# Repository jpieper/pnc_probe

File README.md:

# Pocket NC Probe Support #

This repository contains:

* Hardware designs to integrate a https://vers.by touch probe into the Pocket NC, https://pocketnc.com
* g-code routines for performing probe operations on the Pocket NC

# Usage #

When installed, [G38.x gcode commands](https://linuxcnc.org/docs/2.6/html/gcode/gcode.html#sec:G38-probe) work as expected.  If the jpieper/pnc_probe subroutines are installed, two new gcode programs are available: `pnc-probe-center-id` and `pnc-probe-center-od`.

These scripts probe features that are close to machine X=0,Y=0 and set G54 to the exact center.

To run either, manually position the probe along either the X axis or Y axis just inside (for ID) or just outside (for OD) at the depth you wish to probe.  Leave sufficient margin (~2mm) so that when the probe checks other directions it will have room to plunge without colliding with the work.

Then start the program.

# Installation #

## Hardware ##

Watch the following video:

TODO

1. Attach the adapter housing to the A axis stepper using a cable tie.  The cable tie should be pulled tight, as this helps keep the enclosure sealed from chips.

2. Disconnect the RJ45 cable from the A axis carriage and connect it to the bottom RJ45 port on the adapter.  The 1ft long ethernet cable should then be connected from the A axis carriage to the top port of the adapter.

3. To insert the probe, the A axis MUST be moved out of the home position.  Note, the machine CANNOT BE HOMED while the probe is inserted, or it will crash.

4. Using a dial indicator, adjust the M2 screws accessed through holes in the front of the probe to reduce runout at the tip of the probe.

5. Remove the screw cap from the adapter enclosure, attach the probe cable to the USB port.  Note, this is not actual USB, but that is the cable the vers.by ships with.

6. Attach the magnetic coupled end of the cable to the probe.

7. When removing the probe, be sure to reinstall the USB cap, otherwise chips may fall into the connector.

## Software ##

1. Copy the contents of the `ncfiles/` and `subroutines/` directories to `/home/pocketnc` on the pocketnc.  You can use WinSCP from Windows, or rsync from Mac/Linux.  A suitable command for linux might look like:

```
rsync -Pv ncfiles subroutines pocketnc@192.168.6.2:
```

2. Depending upon your machine version, you may need to add a .ini overlay.

### Kinetic ###

Modern versions of the Kinetic interface require no changes.

### Kinetic (pre 5.1.2) ###

Older versions of Kinetic require the following overlay added.

 * Config Tab
 * Server
 * INI OVERLAY
 * EDIT OVERLAY (bottom right)
 * If RS274NGC is not already in the list of groups, use the '+' button to add it.
 * Ensure the following key is set as follows:

```
SUBROUTINE_PATH=/opt/pocketnc/Settings/subroutines:/home/pocketnc/subroutines
```

 * If you had to change anything, click "REBOOT MACHINE".

### Legacy ###

TODO

# LICENSE #

All files contained in this repository are available under an Apache 2.0 License: https://www.apache.org/licenses/LICENSE-2.0

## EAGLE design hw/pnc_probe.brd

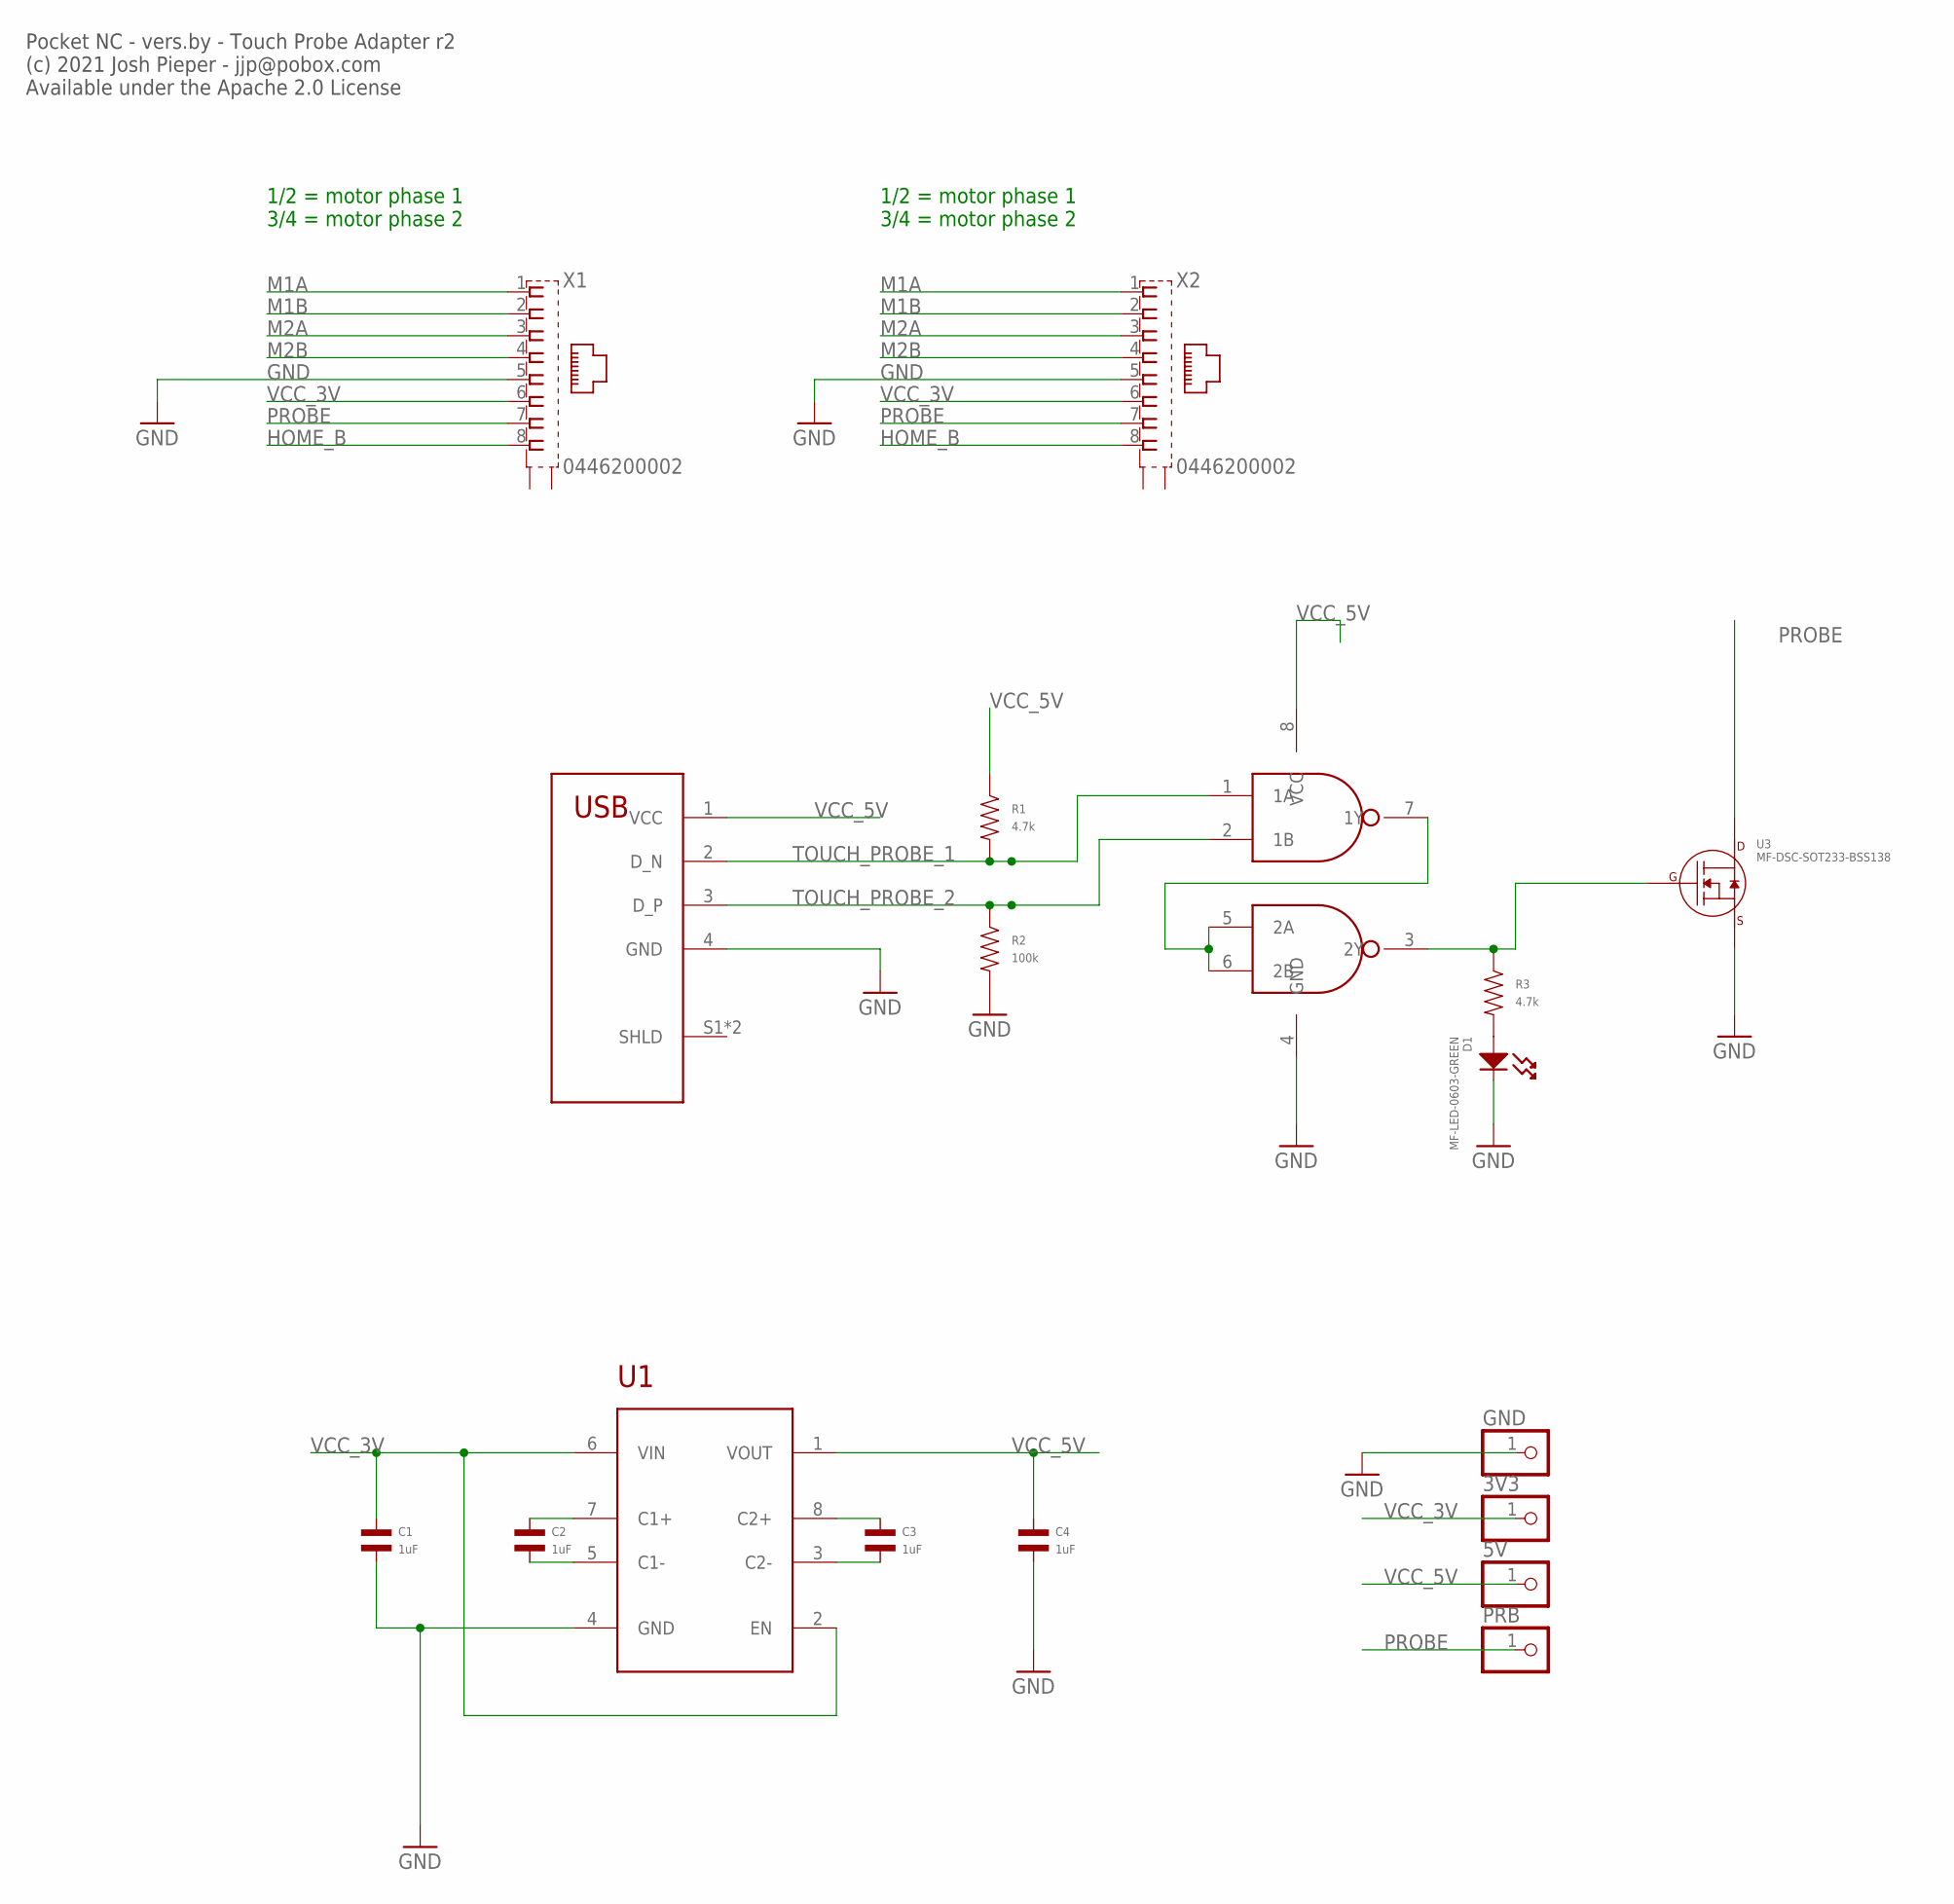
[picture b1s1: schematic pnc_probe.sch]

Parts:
3V3, 5V: PINHD-1X1; 1X01
C1, C2, C3, C4: 1uF; C0603; MPN MF-CAP-0603-1uF
D1: MF-LED-0603-GREEN; LED0603
GND: PINHD-1X1; 1X01
PRB: PINHD-1X1; 1X01
R1: 4.7k; R0603; MPN MF-RES-0603-4.7K
R2: 100k; R0603; MPN MF-RES-0603-100K
R3: 4.7k; R0603; MPN MF-RES-0603-100K
U1: TPS6024X_VSSOP8; VSSOP8
U2: DUAL_NAND_SSOP8; SSOP8; MPN SN74LVC2G00DCTR
U3: MF-DSC-SOT233-BSS138; SOT-23-3
U$1: USBAUSBA; ONSHORE_USBA_1HSXX
X1, X2: 0446200002

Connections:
GND: C1.P$2, C4.P$2, D1.CATHODE, GND.1, R2.P$2, U1.4 (GND), U2.4 (GND), U3.P$2 (SOURCE), U$1.4 (GND), X1.5, X2.5
HOME_B: X1.8, X2.8
M1A: X1.1, X2.1
M1B: X1.2, X2.2
M2A: X1.3, X2.3
M2B: X1.4, X2.4
unnamed: U2.5 (2A), U2.6 (2B), U2.7 (1Y)
unnamed: C2.P$1, U1.7 (C1+)
unnamed: D1.ANODE, R3.P$2
unnamed: R3.P$1, U2.3 (2Y), U3.P$1 (GATE)
unnamed: C2.P$2, U1.5 (C1-)
unnamed: C3.P$1, U1.8 (C2+)
unnamed: C3.P$2, U1.3 (C2-)
PROBE: PRB.1, U3.P$3 (DRAIN), X1.7, X2.7
TOUCH_PROBE_1: R1.P$2, U2.1 (1A), U$1.2 (D_N)
TOUCH_PROBE_2: R2.P$1, U2.2 (1B), U$1.3 (D_P)
VCC_3V: 3V3.1, C1.P$1, U1.2 (EN), U1.6 (VIN), X1.6, X2.6
VCC_5V: 5V.1, C4.P$1, R1.P$1, U1.1 (VOUT), U2.8 (VCC), U$1.1 (VCC)

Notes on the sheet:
1/2 = motor phase 1 3/4 = motor phase 2
Pocket NC - vers.by - Touch Probe Adapter r2 (c) 2021 Josh Pieper - jjp@pobox.com Available under the Apache 2.0 License

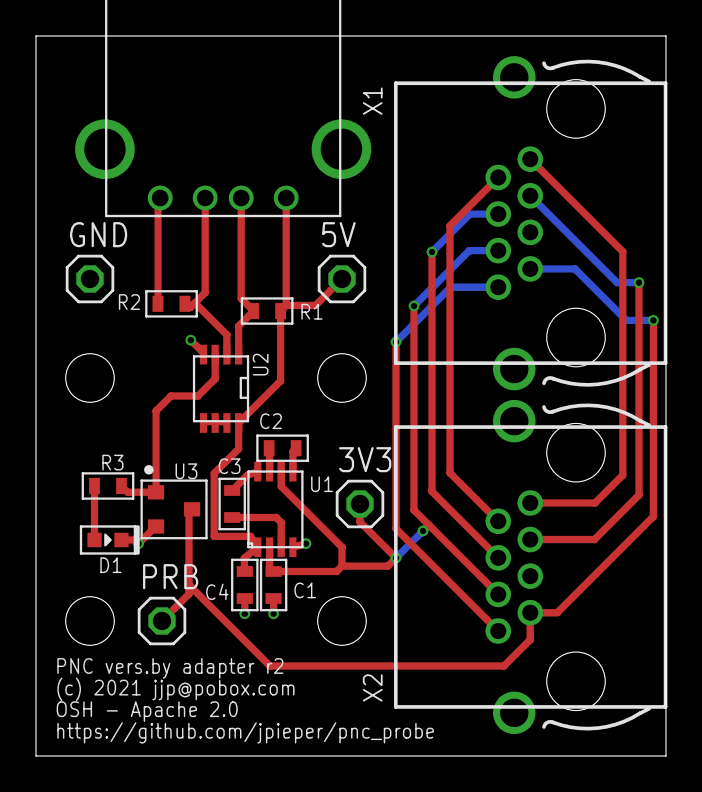
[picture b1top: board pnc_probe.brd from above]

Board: 2 copper layers, 35.0 x 40.0 mm, 18 parts (0 on the bottom side), 18 nets.

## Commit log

2021-08-07 Draft of PCB
2021-08-07 Random enclosure STLs
2021-09-23 Untested beginnings of gcode, a license, and a README
2021-09-23 Rename and robustify the single axis probing script
2021-09-23 A script which probes the OD of a circle or square roughly already centered
2021-09-23 Add some more comments and remove debug statements
2021-09-23 Fix r1 errata
    * The footprint for the TPS6024 was wrong. I wasn't able to find a
    sample one, so used a generic VSSOP originally, but that didn't
    match the TI part. I instead used rough dimensions from a KiCAD
    model and double checked against the datasheet.
    * Yikes, I had left some airwires!
    * Added test points for gnd, power, and the final probe signal.
2021-09-27 Make an ID as well as an OD probe, from the same basic routine
2021-09-28 Tweak offset
2021-11-17 Updates to gcode
2021-11-17 Fix a component value
2021-11-17 More attempts at an enclosure
2021-12-31 r2 as manufactured
2022-01-31 Just include production enclosure 3D prints
2022-01-31 Pull probe offset compensation from config
2022-01-31 Segregate gcode into subroutines and not
2022-01-31 Improve README with actual usage and install instructions
2022-01-31 Improve markdown syntax
2022-02-10 Document that modern Kinetic SW does not require an overlay

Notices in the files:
hw/pnc_probe.brd:
(c) 2021 jjp@pobox.com
